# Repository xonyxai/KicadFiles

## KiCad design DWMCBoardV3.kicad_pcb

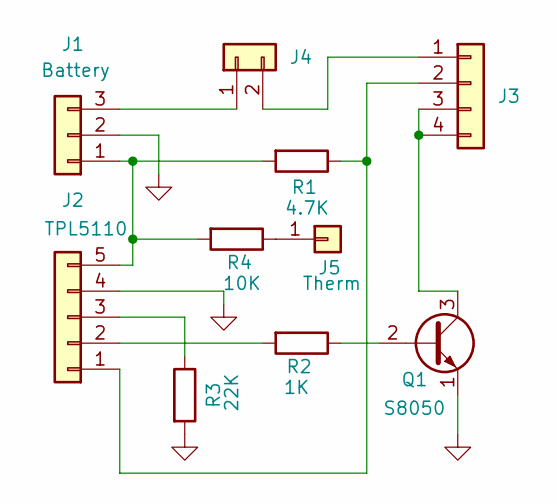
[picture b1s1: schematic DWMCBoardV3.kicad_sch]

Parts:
J1: Battery; PinHeader_1x03_P2.54mm_Vertical
J2: TPL5110; PinHeader_1x05_P2.54mm_Vertical
J3: Conn_01x04; PinHeader_1x04_P2.54mm_Vertical
J4: Conn_01x02; PinHeader_1x02_P2.54mm_Vertical
J5: Therm; PinHeader_1x01_P2.54mm_Vertical
Q1: S8050; TO-92_Inline
R1: 4.7K; R_Axial_DIN0207_L6.3mm_D2.5mm_P10.16mm_Horizontal
R2: 1K; R_Axial_DIN0207_L6.3mm_D2.5mm_P10.16mm_Horizontal
R3: 22K; R_Axial_DIN0207_L6.3mm_D2.5mm_P10.16mm_Horizontal
R4: 10K; R_Axial_DIN0207_L6.3mm_D2.5mm_P10.16mm_Horizontal

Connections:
GND: J1.2, J2.4, Q1.1 (E), R3.2
unnamed: J1.1, J2.5, R1.2, R4.2
unnamed: J1.3, J4.1
unnamed: J2.1, J3.2, R1.1
unnamed: J2.2, R2.2
unnamed: J2.3, R3.1
unnamed: J3.1, J4.2
unnamed: J3.3, J3.4, Q1.3 (C)
unnamed: J5.1, R4.1
unnamed: Q1.2 (B), R2.1

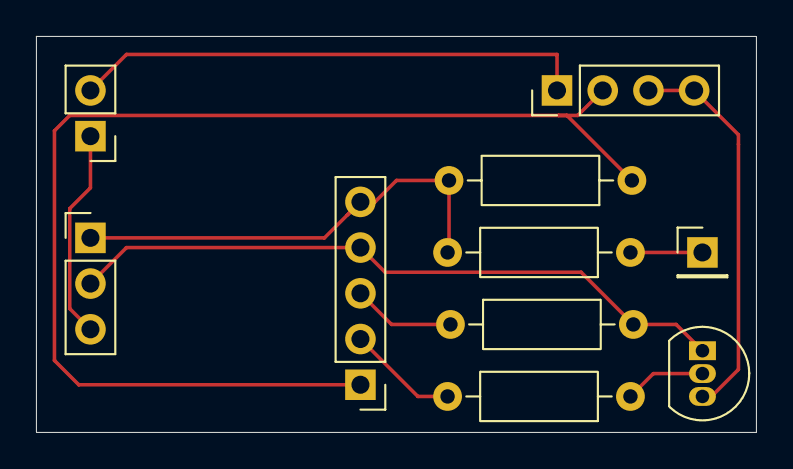
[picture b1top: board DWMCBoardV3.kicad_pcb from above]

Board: 2 copper layers, 40.0 x 22.0 mm, 10 parts (0 on the bottom side), 10 nets.

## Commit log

2025-08-24 Cad Files
